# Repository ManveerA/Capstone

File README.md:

Repository for Team 34's Capstone project: Demonstration of Electromechanical Relationships in a Controlled Electric Motor.

Team 34 Members:

Manveer Aujla - manveeraujla0226@gmail.com

Gavin Feher - gavin.feher@gmail.com

Adam DePinto - depintoadam@gmail.com

Last updated: 2025-08-01

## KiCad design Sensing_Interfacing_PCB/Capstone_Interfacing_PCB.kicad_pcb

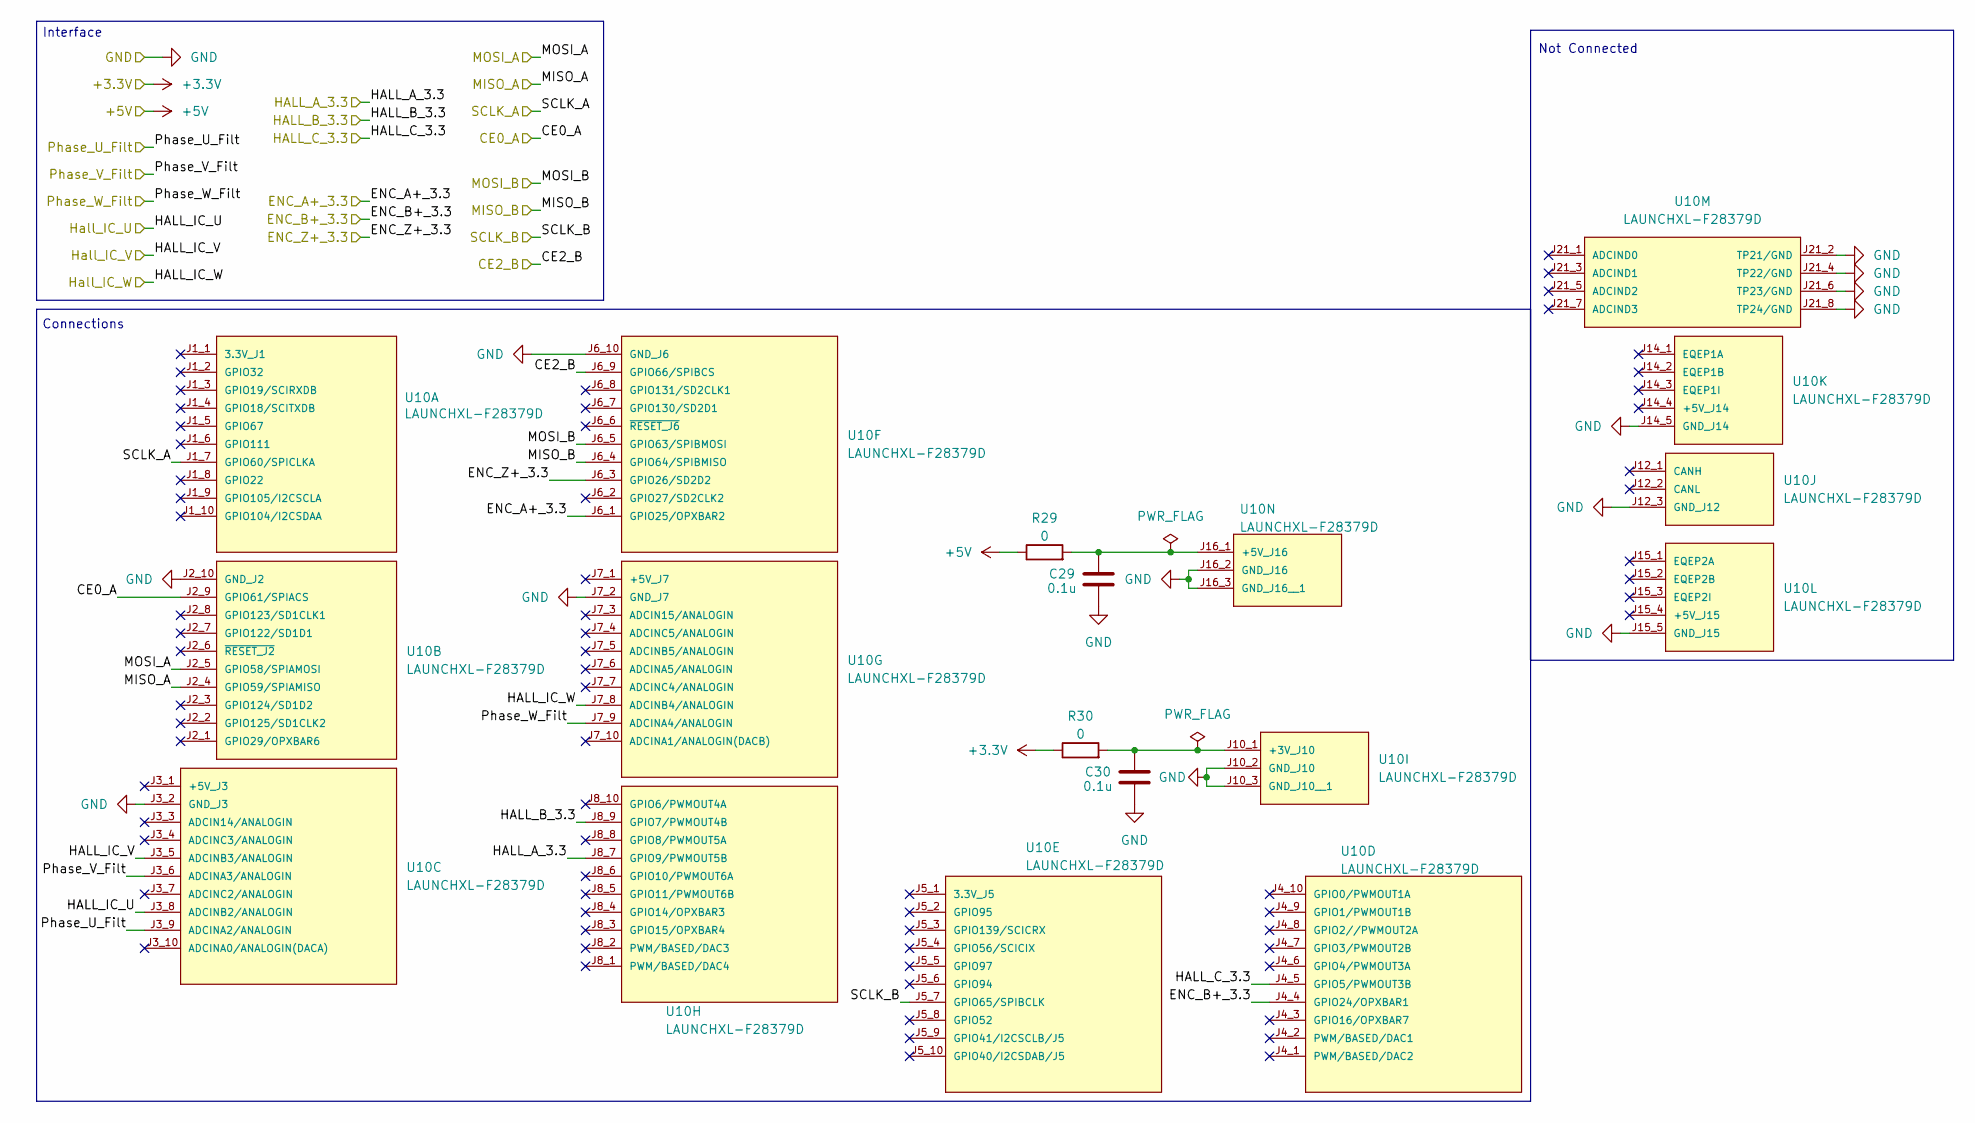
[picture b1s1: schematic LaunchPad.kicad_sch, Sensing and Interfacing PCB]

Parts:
C29, C30: 0.1u; C_1206_3216Metric_Pad1.33x1.80mm_HandSolder; Part Number C1206C104K4RACTU
R29, R30: 0; R_1206_3216Metric_Pad1.30x1.75mm_HandSolder; Part Number RMCF1206ZT0R00
U10: LAUNCHXL-F28379D; MOD_LAUNCHXL-F28379D; PARTREV 2.0

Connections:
+3.3V: R30.1; also elsewhere on the board
+5V: R29.1; also elsewhere on the board
/Input Stage/ENC_A+_3.3: U10.J6_1 (GPIO25/OPXBAR2); also elsewhere on the board
/Input Stage/ENC_B+_3.3: U10.J4_4 (GPIO24/OPXBAR1); also elsewhere on the board
/Input Stage/ENC_Z+_3.3: U10.J6_3 (GPIO26/SD2D2); also elsewhere on the board
/Input Stage/HALL_A_3.3: U10.J8_7 (GPIO9/PWMOUT5B); also elsewhere on the board
/Input Stage/HALL_B_3.3: U10.J8_9 (GPIO7/PWMOUT4B); also elsewhere on the board
/Input Stage/HALL_C_3.3: U10.J4_5 (GPIO5/PWMOUT3B); also elsewhere on the board
/Input Stage/HALL_IC_U: U10.J3_8 (ADCINB2/ANALOGIN); also elsewhere on the board
/Input Stage/HALL_IC_V: U10.J3_5 (ADCINB3/ANALOGIN); also elsewhere on the board
/Input Stage/HALL_IC_W: U10.J7_8 (ADCINB4/ANALOGIN); also elsewhere on the board
/Input Stage/Phase_U_Filt: U10.J3_9 (ADCINA2/ANALOGIN); also elsewhere on the board
/Input Stage/Phase_V_Filt: U10.J3_6 (ADCINA3/ANALOGIN); also elsewhere on the board
/Input Stage/Phase_W_Filt: U10.J7_9 (ADCINA4/ANALOGIN); also elsewhere on the board
/LaunchPad/CE0_A: U10.J2_9 (GPIO61/SPIACS); also elsewhere on the board
/LaunchPad/CE2_B: U10.J6_9 (GPIO66/SPIBCS); also elsewhere on the board
/LaunchPad/MISO_A: U10.J2_4 (GPIO59/SPIAMISO); also elsewhere on the board
/LaunchPad/MISO_B: U10.J6_4 (GPIO64/SPIBMISO); also elsewhere on the board
/LaunchPad/MOSI_A: U10.J2_5 (GPIO58/SPIAMOSI); also elsewhere on the board
/LaunchPad/MOSI_B: U10.J6_5 (GPIO63/SPIBMOSI); also elsewhere on the board
/LaunchPad/SCLK_A: U10.J1_7 (GPIO60/SPICLKA); also elsewhere on the board
/LaunchPad/SCLK_B: U10.J5_7 (GPIO65/SPIBCLK); also elsewhere on the board
GND: C29.2, C30.2, U10.J2_10 (GND_J2), U10.J3_2 (GND_J3), U10.J6_10 (GND_J6), U10.J7_2 (GND_J7), U10.J10_2 (GND_J10), U10.J10_3 (GND_J10__1), U10.J12_3 (GND_J12), U10.J14_5 (GND_J14), U10.J15_5 (GND_J15), U10.J16_2 (GND_J16), U10.J16_3 (GND_J16__1), U10.J21_2 (TP21/GND), U10.J21_4 (TP22/GND), U10.J21_6 (TP23/GND), U10.J21_8 (TP24/GND); also elsewhere on the board
unnamed: C30.1, R30.2, U10.J10_1 (+3V_J10)
unnamed: C29.1, R29.2, U10.J16_1 (+5V_J16)

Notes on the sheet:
Connections
Not Connected
Interface

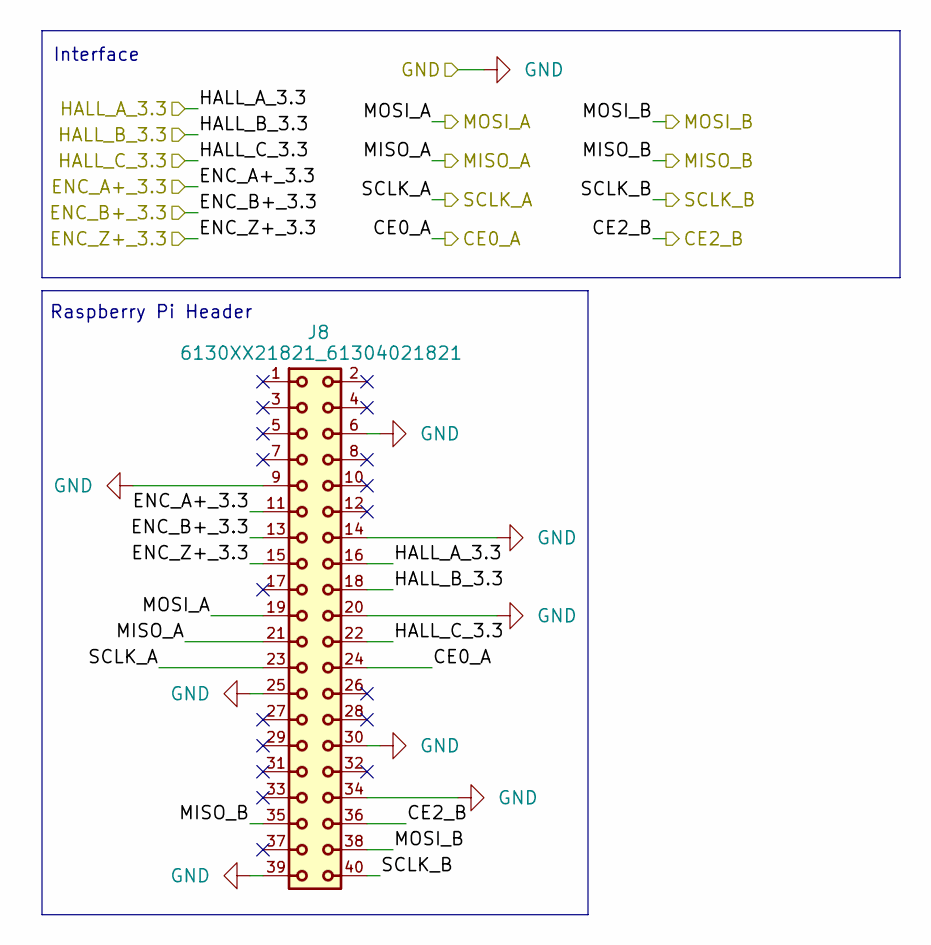
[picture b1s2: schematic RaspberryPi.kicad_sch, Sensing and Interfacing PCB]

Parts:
J8: 6130XX21821_61304021821; 61304021821; Part Number 61304021821

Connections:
/Input Stage/ENC_A+_3.3: J8.11; also elsewhere on the board
/Input Stage/ENC_B+_3.3: J8.13; also elsewhere on the board
/Input Stage/ENC_Z+_3.3: J8.15; also elsewhere on the board
/Input Stage/HALL_A_3.3: J8.16; also elsewhere on the board
/Input Stage/HALL_B_3.3: J8.18; also elsewhere on the board
/Input Stage/HALL_C_3.3: J8.22; also elsewhere on the board
/LaunchPad/CE0_A: J8.24; also elsewhere on the board
/LaunchPad/CE2_B: J8.36; also elsewhere on the board
/LaunchPad/MISO_A: J8.21; also elsewhere on the board
/LaunchPad/MISO_B: J8.35; also elsewhere on the board
/LaunchPad/MOSI_A: J8.19; also elsewhere on the board
/LaunchPad/MOSI_B: J8.38; also elsewhere on the board
/LaunchPad/SCLK_A: J8.23; also elsewhere on the board
/LaunchPad/SCLK_B: J8.40; also elsewhere on the board
GND: J8.6, J8.9, J8.14, J8.20, J8.25, J8.30, J8.34, J8.39; also elsewhere on the board

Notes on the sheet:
Interface
Raspberry Pi Header

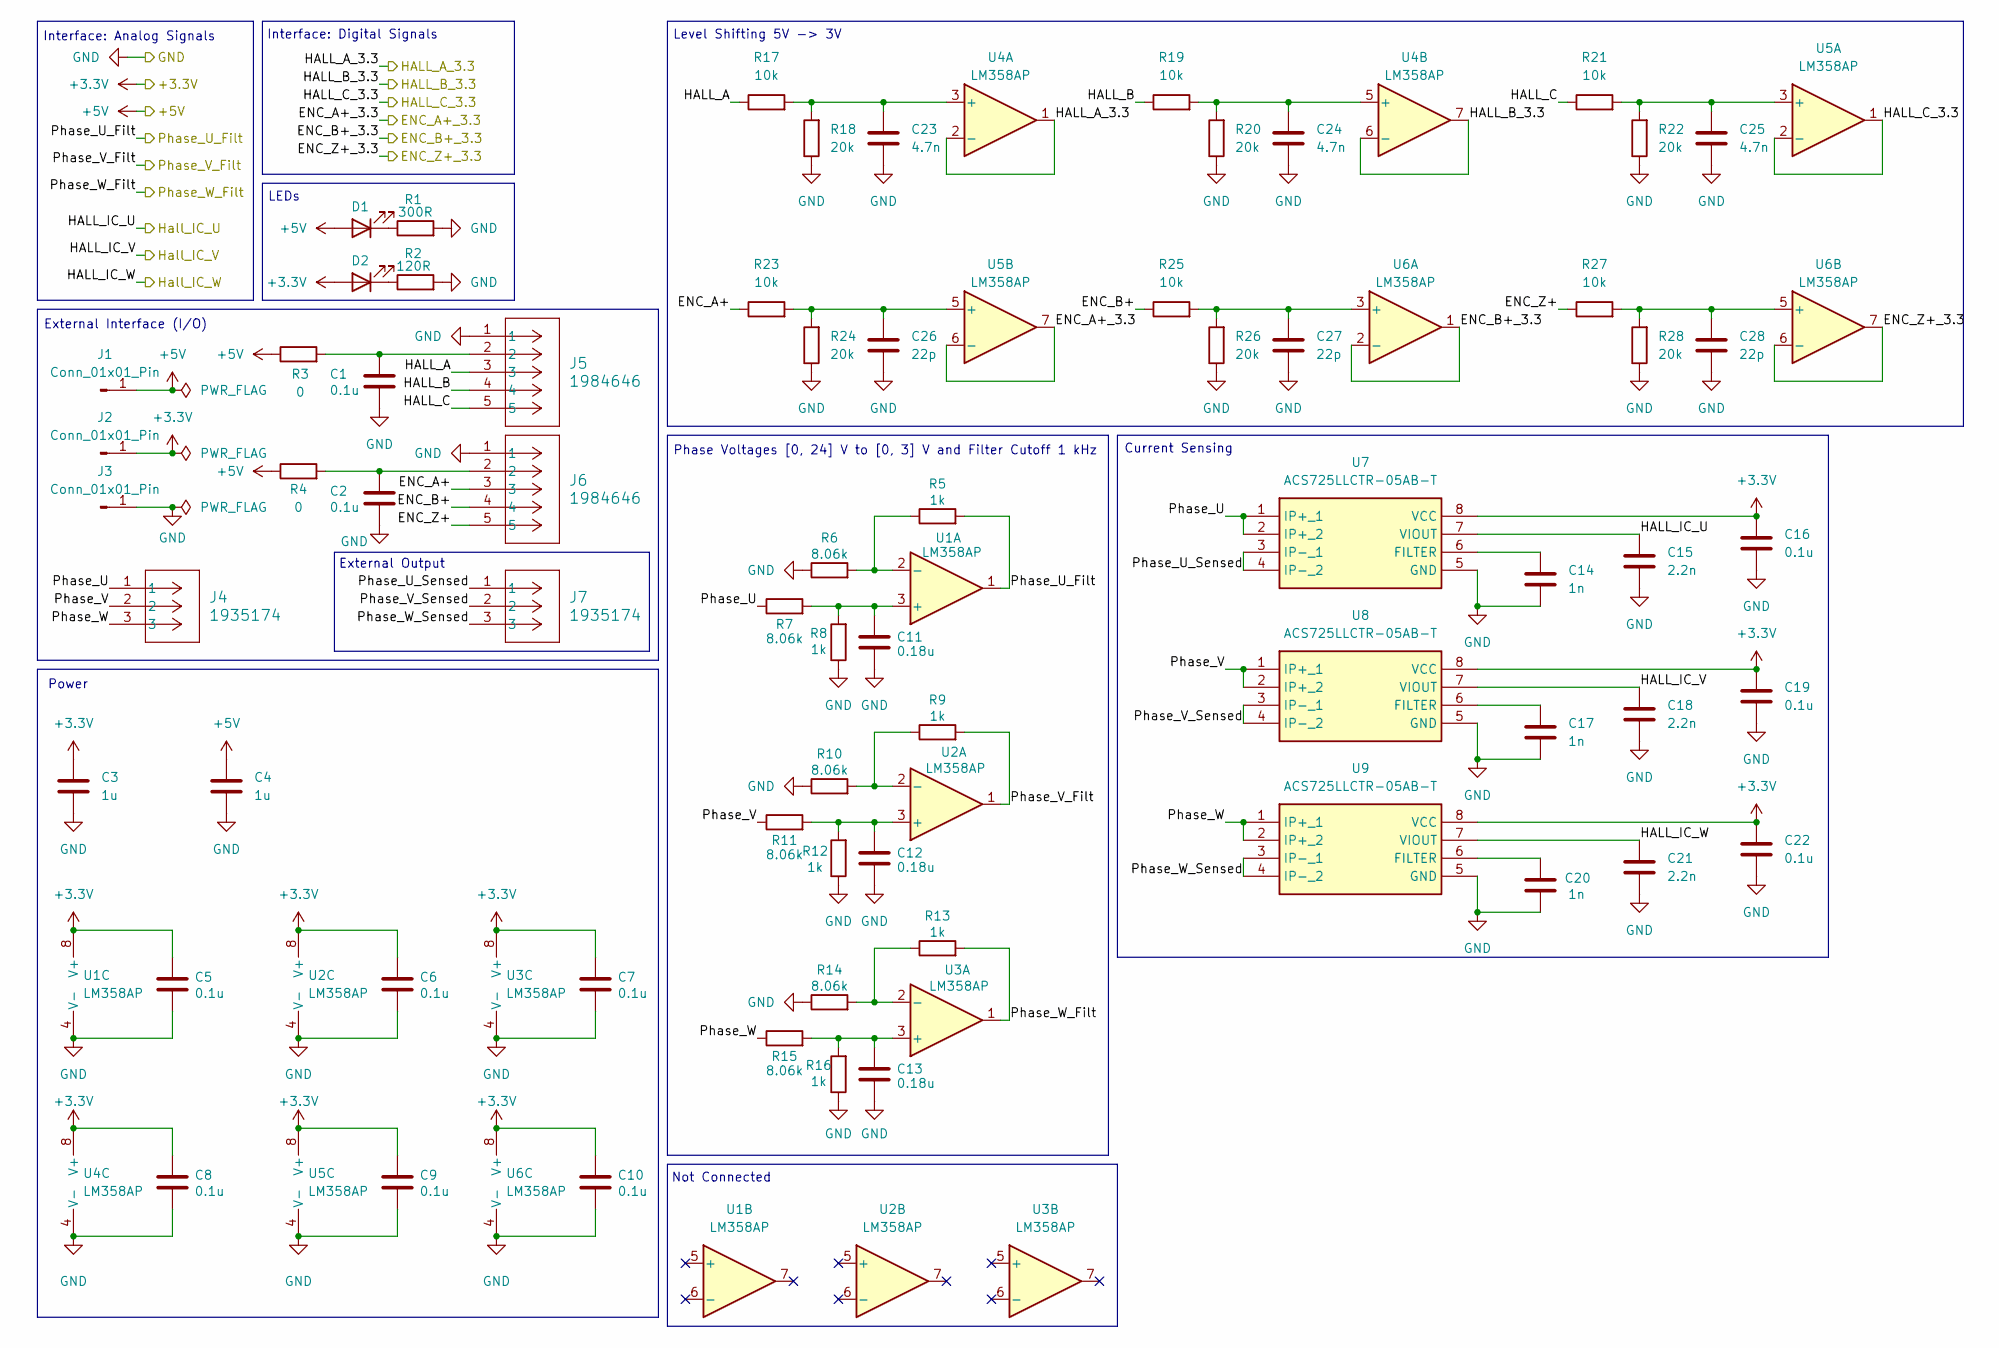
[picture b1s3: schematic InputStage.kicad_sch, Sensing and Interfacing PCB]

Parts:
C1, C2, C5, C6, C7, C8, C9, C10, C16, C19, C22: 0.1u; C_1206_3216Metric_Pad1.33x1.80mm_HandSolder; Part Number C1206C104K4RACTU
C3: 1u; C_1206_3216Metric_Pad1.33x1.80mm_HandSolder; Part Number GRM319R71A105KA01D
C4: 1u; C_1206_3216Metric_Pad1.33x1.80mm_HandSolder; Part Number GRM319R71C105KAA3D
C11, C12, C13: 0.18u; C_1206_3216Metric_Pad1.33x1.80mm_HandSolder; Part Number CC1206KKX7R9BB184
C14, C17, C20: 1n; C_1206_3216Metric_Pad1.33x1.80mm_HandSolder; Part Number CC1206FRNPO9BN102
C15, C18, C21: 2.2n; C_1206_3216Metric_Pad1.33x1.80mm_HandSolder; Part Number C1206C222K4HACAUTO
C23, C24, C25: 4.7n; C_1206_3216Metric_Pad1.33x1.80mm_HandSolder; Part Number 885012208025
C26, C27, C28: 22p; C_1206_3216Metric_Pad1.33x1.80mm_HandSolder; Part Number C1206C220F4HACTU
D1, D2: LTST-C150GKT; LED_1206_3216Metric_Pad1.42x1.75mm_HandSolder; Part Number LTST-C150GKT
J1, J2, J3: Conn_01x01_Pin; Banana_Jack_1Pin; Part Number BU-P72930-2
J4, J7: 1935174; CONN_1935174_PXC; Part Number 1935174
J5, J6: 1984646; CONN_1984646_PXC; Part Number 1984646
R1: 300R; R_1206_3216Metric_Pad1.30x1.75mm_HandSolder; Part Number RMCF1206FT300R
R2: 120R; R_1206_3216Metric_Pad1.30x1.75mm_HandSolder; Part Number RMCF1206FT120R
R3, R4: 0; R_1206_3216Metric_Pad1.30x1.75mm_HandSolder; Part Number RMCF1206ZT0R00
R5, R8, R9, R12, R13, R16: 1k; R_1206_3216Metric_Pad1.30x1.75mm_HandSolder; Part Number RNCP1206FTD1K00
R6, R7, R10, R11, R14, R15: 8.06k; R_1206_3216Metric_Pad1.30x1.75mm_HandSolder; Part Number RNCP1206FTD8K06
R17, R19, R21, R23, R25, R27: 10k; R_1206_3216Metric_Pad1.30x1.75mm_HandSolder; Part Number RNCF1206DTE10K0
R18, R20, R22, R24, R26, R28: 20k; R_1206_3216Metric_Pad1.30x1.75mm_HandSolder; Part Number RNCF1206BTE20K0
U1, U2, U3, U4, U5, U6: LM358AP; DIP794W45P254L959H508Q8; Part Number LM358AP
U7, U8, U9: ACS725LLCTR-05AB-T; SOIC127P600X175-8N; Mouser Part Number 250-725LLCTR05ABT

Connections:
+3.3V: C3.1, C5.1, C6.1, C7.1, C8.1, C9.1, C10.1, C16.1, C19.1, C22.1, D2.2 (A), J2.1, U1.8 (V+), U2.8 (V+), U3.8 (V+), U4.8 (V+), U5.8 (V+), U6.8 (V+), U7.8 (VCC), U8.8 (VCC), U9.8 (VCC); also elsewhere on the board
+5V: C4.1, D1.2 (A), J1.1, R3.1, R4.1; also elsewhere on the board
/Input Stage/ENC_A+: J6.3, R23.1
/Input Stage/ENC_A+_3.3: U5.6 (-), U5.7; also elsewhere on the board
/Input Stage/ENC_B+: J6.4, R25.1
/Input Stage/ENC_B+_3.3: U6.1, U6.2 (-); also elsewhere on the board
/Input Stage/ENC_Z+: J6.5, R27.1
/Input Stage/ENC_Z+_3.3: U6.6 (-), U6.7; also elsewhere on the board
/Input Stage/HALL_A: J5.3, R17.1
/Input Stage/HALL_A_3.3: U4.1, U4.2 (-); also elsewhere on the board
/Input Stage/HALL_B: J5.4, R19.1
/Input Stage/HALL_B_3.3: U4.6 (-), U4.7; also elsewhere on the board
/Input Stage/HALL_C: J5.5, R21.1
/Input Stage/HALL_C_3.3: U5.1, U5.2 (-); also elsewhere on the board
/Input Stage/HALL_IC_U: C15.1, U7.7 (VIOUT); also elsewhere on the board
/Input Stage/HALL_IC_V: C18.1, U8.7 (VIOUT); also elsewhere on the board
/Input Stage/HALL_IC_W: C21.1, U9.7 (VIOUT); also elsewhere on the board
/Input Stage/Phase_U: J4.1, R7.1, U7.1 (IP+_1), U7.2 (IP+_2)
/Input Stage/Phase_U_Filt: R5.2, U1.1; also elsewhere on the board
/Input Stage/Phase_U_Sensed: J7.1, U7.3 (IP-_1), U7.4 (IP-_2)
/Input Stage/Phase_V: J4.2, R11.1, U8.1 (IP+_1), U8.2 (IP+_2)
/Input Stage/Phase_V_Filt: R9.2, U2.1; also elsewhere on the board
/Input Stage/Phase_V_Sensed: J7.2, U8.3 (IP-_1), U8.4 (IP-_2)
/Input Stage/Phase_W: J4.3, R15.1, U9.1 (IP+_1), U9.2 (IP+_2)
/Input Stage/Phase_W_Filt: R13.2, U3.1; also elsewhere on the board
/Input Stage/Phase_W_Sensed: J7.3, U9.3 (IP-_1), U9.4 (IP-_2)
GND: C1.2, C2.2, C3.2, C4.2, C5.2, C6.2, C7.2, C8.2, C9.2, C10.2, C11.2, C12.2, C13.2, C14.2, C15.2, C16.2, C17.2, C18.2, C19.2, C20.2, C21.2, C22.2, C23.2, C24.2, C25.2, C26.2, C27.2, C28.2, J3.1, J5.1, J6.1, R1.2, R2.2, R6.1, R8.1, R10.1, R12.1, R14.1, R16.1, R18.1, R20.1, R22.1, R24.1, R26.1, R28.1, U1.4 (V-), U2.4 (V-), U3.4 (V-), U4.4 (V-), U5.4 (V-), U6.4 (V-), U7.5 (GND), U8.5 (GND), U9.5 (GND); also elsewhere on the board
unnamed: C1.1, J5.2, R3.2
unnamed: C2.1, J6.2, R4.2
unnamed: D1.1 (K), R1.1
unnamed: D2.1 (K), R2.1
unnamed: C11.1, R7.2, R8.2, U1.3 (+)
unnamed: R5.1, R6.2, U1.2 (-)
unnamed: C12.1, R11.2, R12.2, U2.3 (+)
unnamed: R9.1, R10.2, U2.2 (-)
unnamed: C13.1, R15.2, R16.2, U3.3 (+)
unnamed: R13.1, R14.2, U3.2 (-)
unnamed: C23.1, R17.2, R18.2, U4.3 (+)
unnamed: C24.1, R19.2, R20.2, U4.5 (+)
unnamed: C25.1, R21.2, R22.2, U5.3 (+)
unnamed: C26.1, R23.2, R24.2, U5.5 (+)
unnamed: C27.1, R25.2, R26.2, U6.3 (+)
unnamed: C28.1, R27.2, R28.2, U6.5 (+)
unnamed: C14.1, U7.6 (FILTER)
unnamed: C17.1, U8.6 (FILTER)
unnamed: C20.1, U9.6 (FILTER)

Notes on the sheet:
Interface: Digital Signals
External Output
Power
Phase Voltages [0, 24] V to [0, 3] V and Filter Cutoff 1 kHz
LEDs
External Interface (I/O)
Current Sensing
Interface: Analog Signals
Level Shifting 5V -> 3V
Not Connected

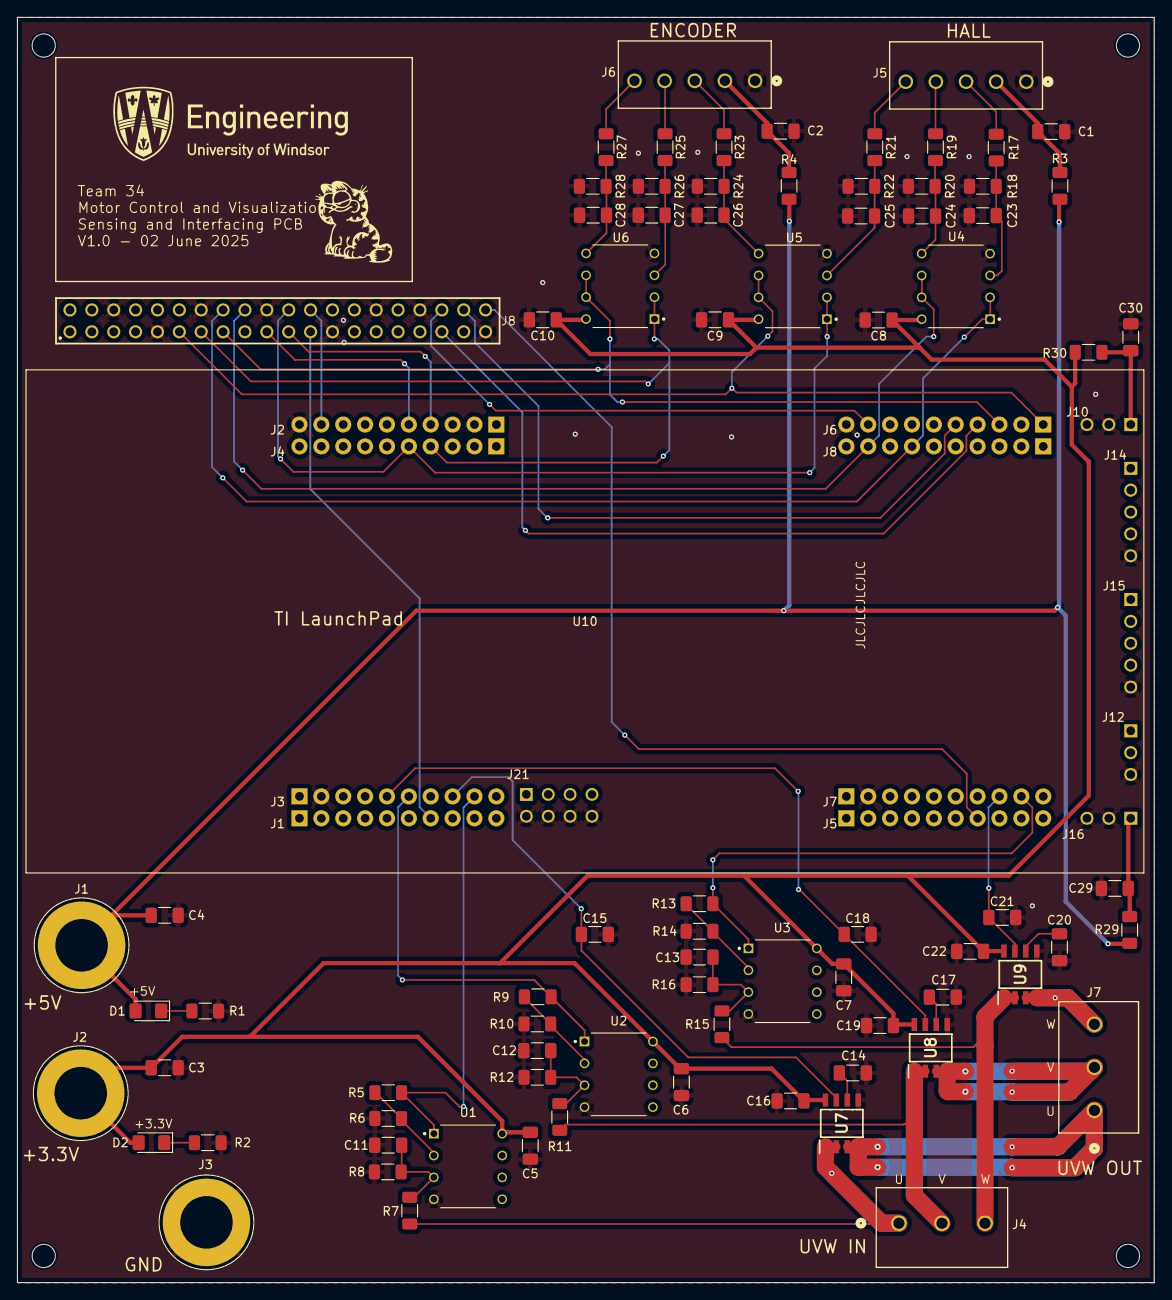
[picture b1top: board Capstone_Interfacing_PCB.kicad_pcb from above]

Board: 2 copper layers, 132.0 x 146.9 mm, 80 parts (0 on the bottom side), 56 nets.

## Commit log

2025-07-31 Rename ReadME to README
2025-07-31 Update and rename ReadME to README
2025-07-31 Create Oscilloscope_Data
2025-07-31 Removed redundant code
